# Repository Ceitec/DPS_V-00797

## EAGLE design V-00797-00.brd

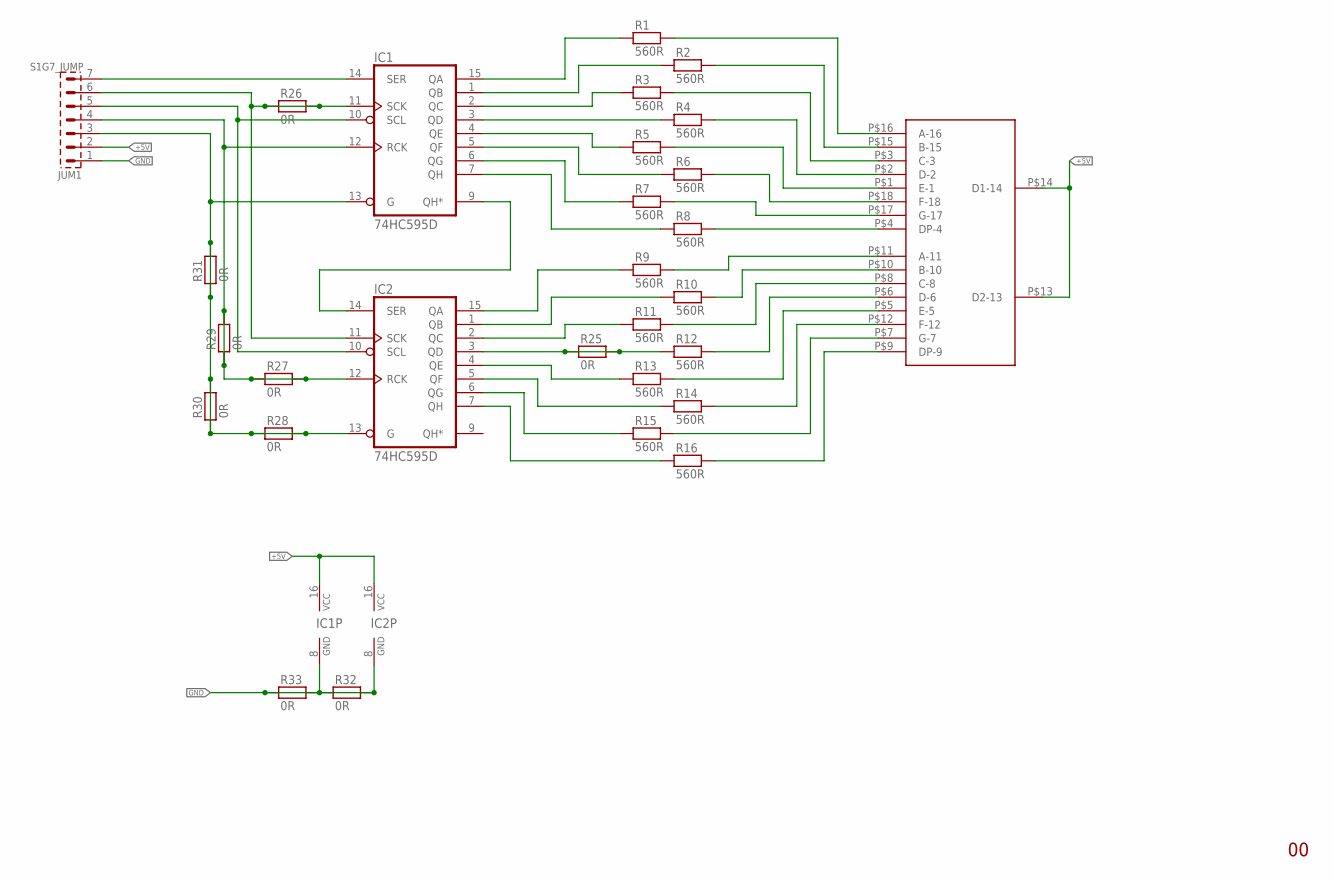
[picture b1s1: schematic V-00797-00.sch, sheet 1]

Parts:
IC1, IC2: 74HC595D; SO16
JUM1: S1G7_JUMP; S1G7_JUM
R1, R2, R3, R4, R5, R6, R7, R8, R9, R10, R11, R12, R13, R14, R15, R16: 560R; 1206
R25, R26, R27, R28, R29, R30, R31, R32, R33: 0R; 1206
U$1: BD-A544RD

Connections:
+5V: IC1.16 (VCC), IC2.16 (VCC), JUM1.2, U$1.P$13 (D2-13), U$1.P$14 (D1-14); also elsewhere on the board
GND: IC1.8 (GND), IC2.8 (GND), JUM1.1, R32.1, R32.2, R33.1, R33.2; also elsewhere on the board
unnamed: R1.2, U$1.P$16 (A-16)
unnamed: R2.2, U$1.P$15 (B-15)
unnamed: R3.2, U$1.P$3 (C-3)
unnamed: R4.2, U$1.P$2 (D-2)
unnamed: R5.2, U$1.P$1 (E-1)
unnamed: R6.2, U$1.P$18 (F-18)
unnamed: R7.2, U$1.P$17 (G-17)
unnamed: R8.2, U$1.P$4 (DP-4)
unnamed: IC1.9 (QH*), IC2.14 (SER)
unnamed: IC1.15 (QA), R1.1
unnamed: IC1.1 (QB), R2.1
unnamed: IC1.2 (QC), R3.1
unnamed: IC1.3 (QD), R4.1
unnamed: IC1.4 (QE), R5.1
unnamed: IC1.5 (QF), R6.1
unnamed: IC1.6 (QG), R7.1
unnamed: IC1.7 (QH), R8.1
unnamed: IC2.1 (QB), R10.1
unnamed: IC2.2 (QC), R11.1
unnamed: IC2.3 (QD), R12.1, R25.1, R25.2
unnamed: IC2.15 (QA), R9.1
unnamed: IC2.7 (QH), R16.1
unnamed: IC2.6 (QG), R15.1
unnamed: IC2.5 (QF), R14.1
unnamed: IC2.4 (QE), R13.1
unnamed: R9.2, U$1.P$11 (A-11)
unnamed: R10.2, U$1.P$10 (B-10)
unnamed: R11.2, U$1.P$8 (C-8)
unnamed: R12.2, U$1.P$6 (D-6)
unnamed: R13.2, U$1.P$5 (E-5)
unnamed: R14.2, U$1.P$12 (F-12)
unnamed: R15.2, U$1.P$7 (G-7)
unnamed: R16.2, U$1.P$9 (DP-9)
unnamed: IC1.14 (SER), JUM1.7
unnamed: IC1.11 (SCK), IC2.11 (SCK), JUM1.6, R26.1, R26.2
unnamed: IC1.10 (SCL), IC2.10 (SCL), JUM1.5
unnamed: IC1.12 (RCK), IC2.12 (RCK), JUM1.4, R27.1, R27.2, R29.1, R29.2
unnamed: IC1.13 (G), IC2.13 (G), JUM1.3, R28.1, R28.2, R30.1, R30.2, R31.1, R31.2

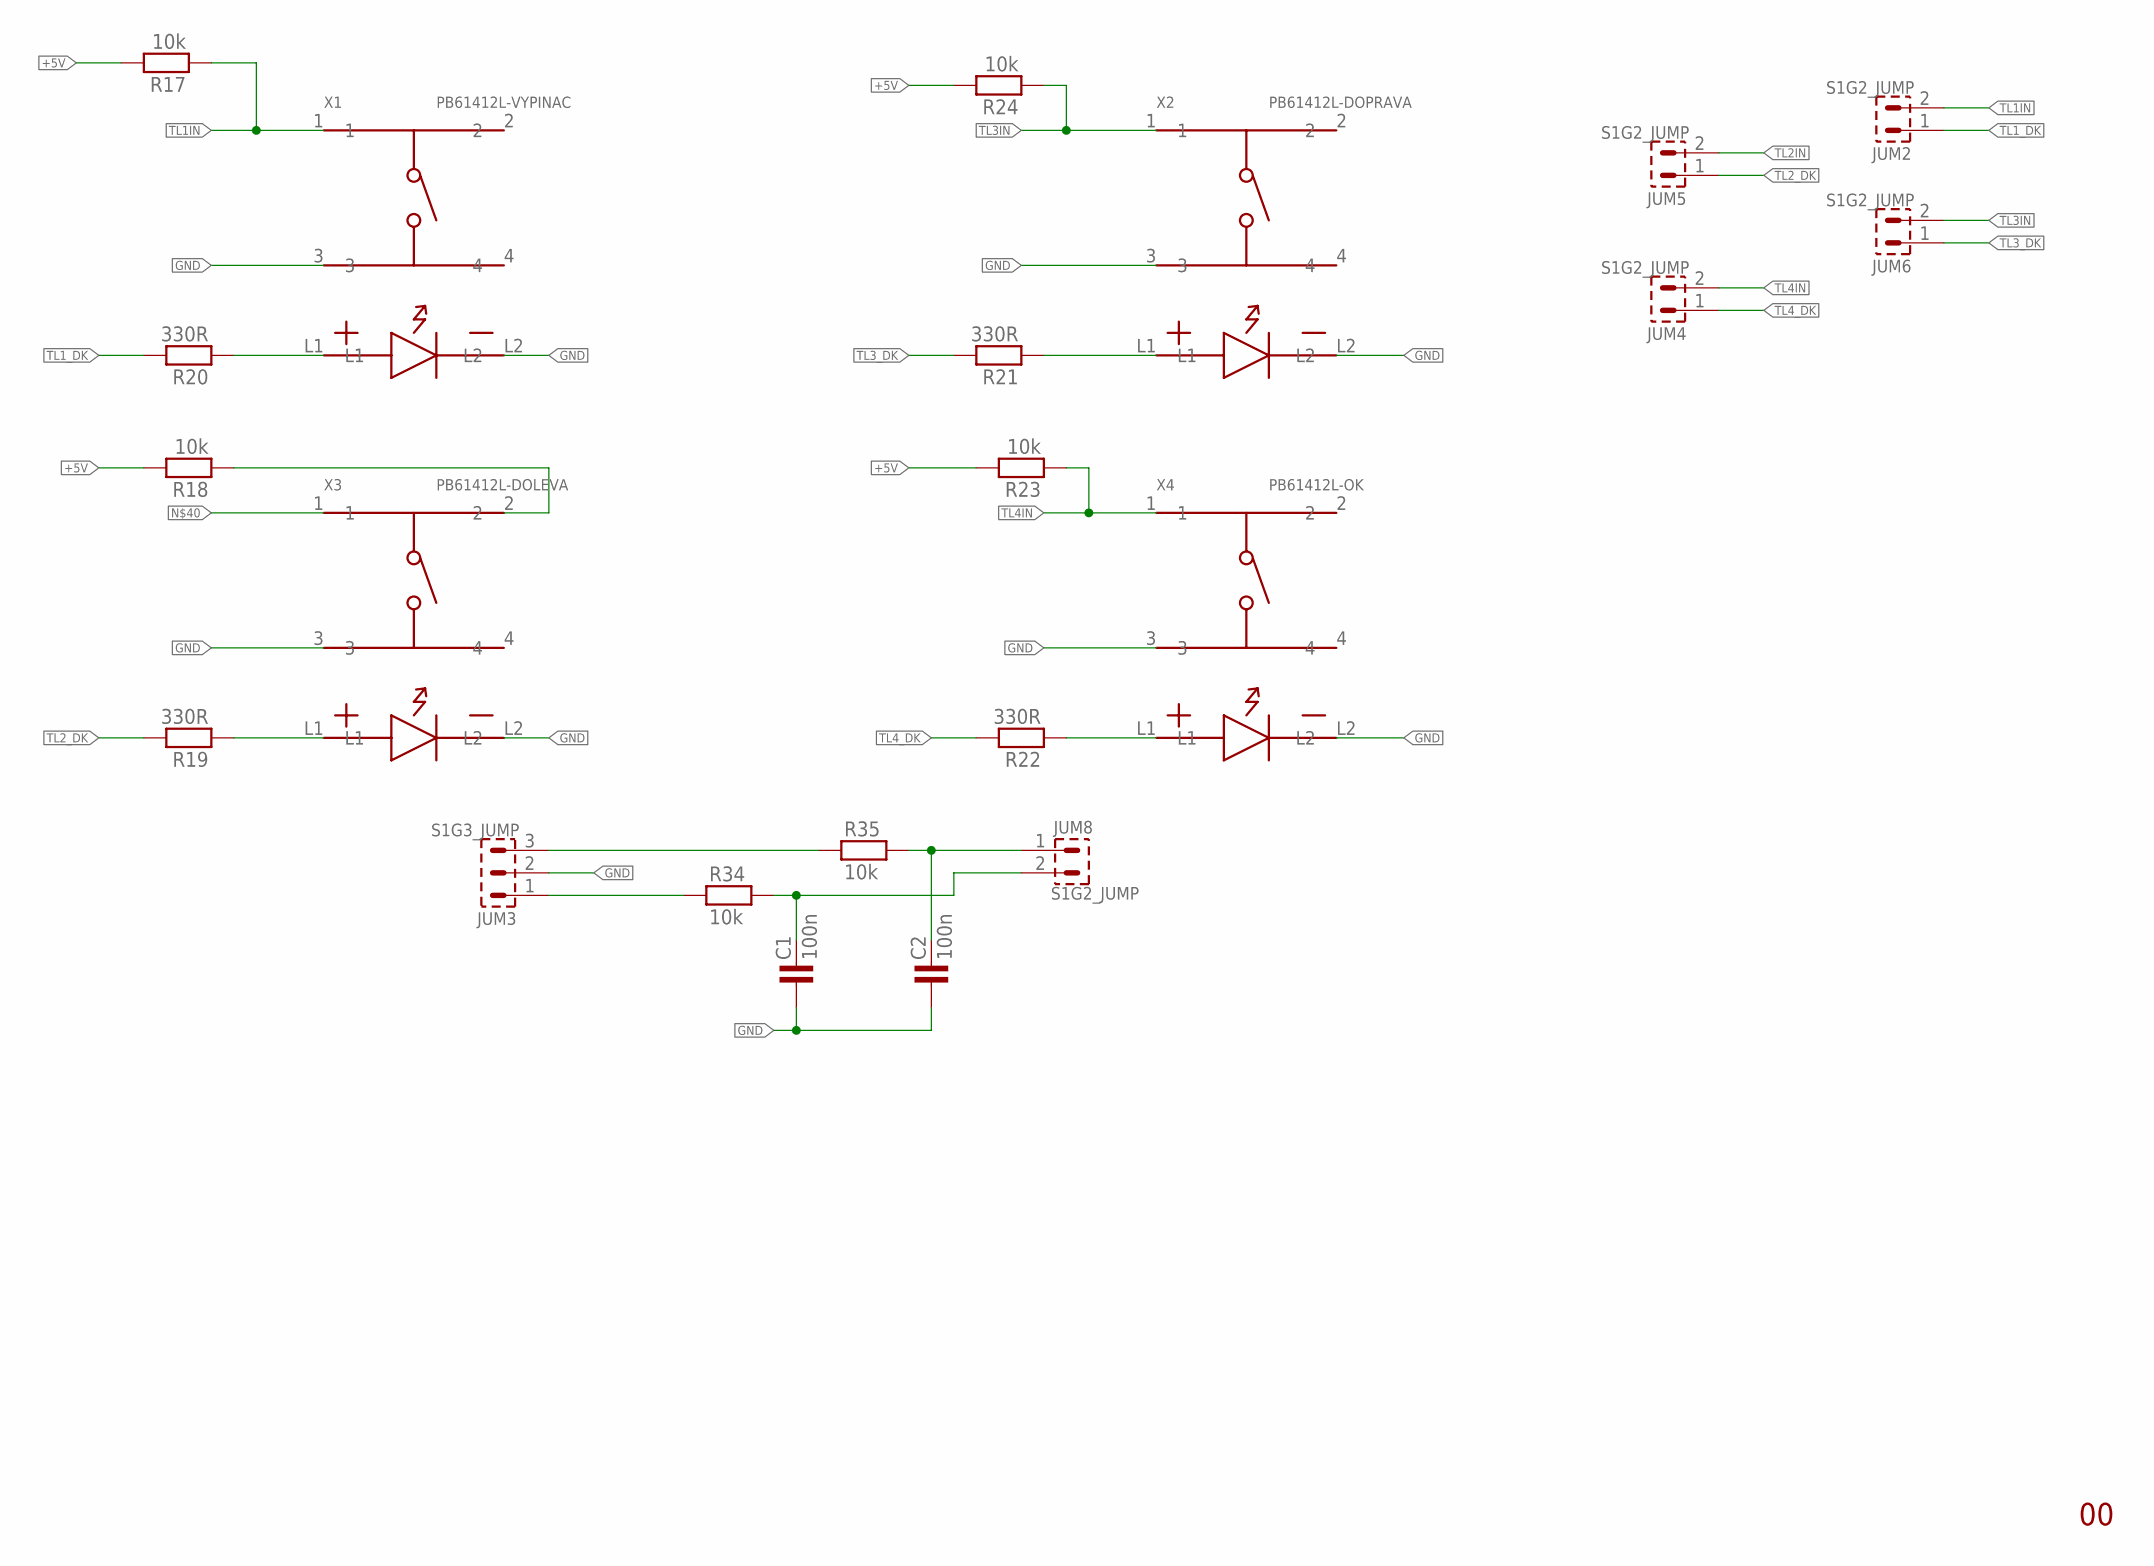
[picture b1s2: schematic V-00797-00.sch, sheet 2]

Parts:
C1, C2: 100n; 1206
JUM2, JUM4, JUM5, JUM6, JUM8: S1G2_JUMP; S1G2_JUM
JUM3: S1G3_JUMP; S1G3_JUM
R17, R18, R23, R24, R34, R35: 10k; 1206
R19, R20, R21, R22: 330R; 1206
X1: PB61412L-VYPINAC; PB1412L-101
X2: PB61412L-DOPRAVA; PB1412L-101
X3: PB61412L-DOLEVA; PB1412L-101
X4: PB61412L-OK; PB1412L-101

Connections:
+5V: R17.2, R18.2, R23.2, R24.2; also elsewhere on the board
ENCODER_A: JUM3.3, R35.1
ENCODER_B: JUM3.1, R34.1
GND: C1.1, C2.1, JUM3.2, X1.3, X1.L2, X2.3, X2.L2, X3.3, X3.L2, X4.3, X4.L2; also elsewhere on the board
INT1: C2.2, JUM8.1, R35.2
unnamed: R20.1, X1.L1
unnamed: R21.1, X2.L1
unnamed: R19.1, X3.L1
unnamed: R22.1, X4.L1
OCB1: C1.2, JUM8.2, R34.2
TL1IN: JUM2.2, R17.1, X1.1
TL1_DK: JUM2.1, R20.2
TL2IN: JUM5.2, R18.1, X3.2
TL2_DK: JUM5.1, R19.2
TL3IN: JUM6.2, R24.1, X2.1
TL3_DK: JUM6.1, R21.2
TL4IN: JUM4.2, R23.1, X4.1
TL4_DK: JUM4.1, R22.2

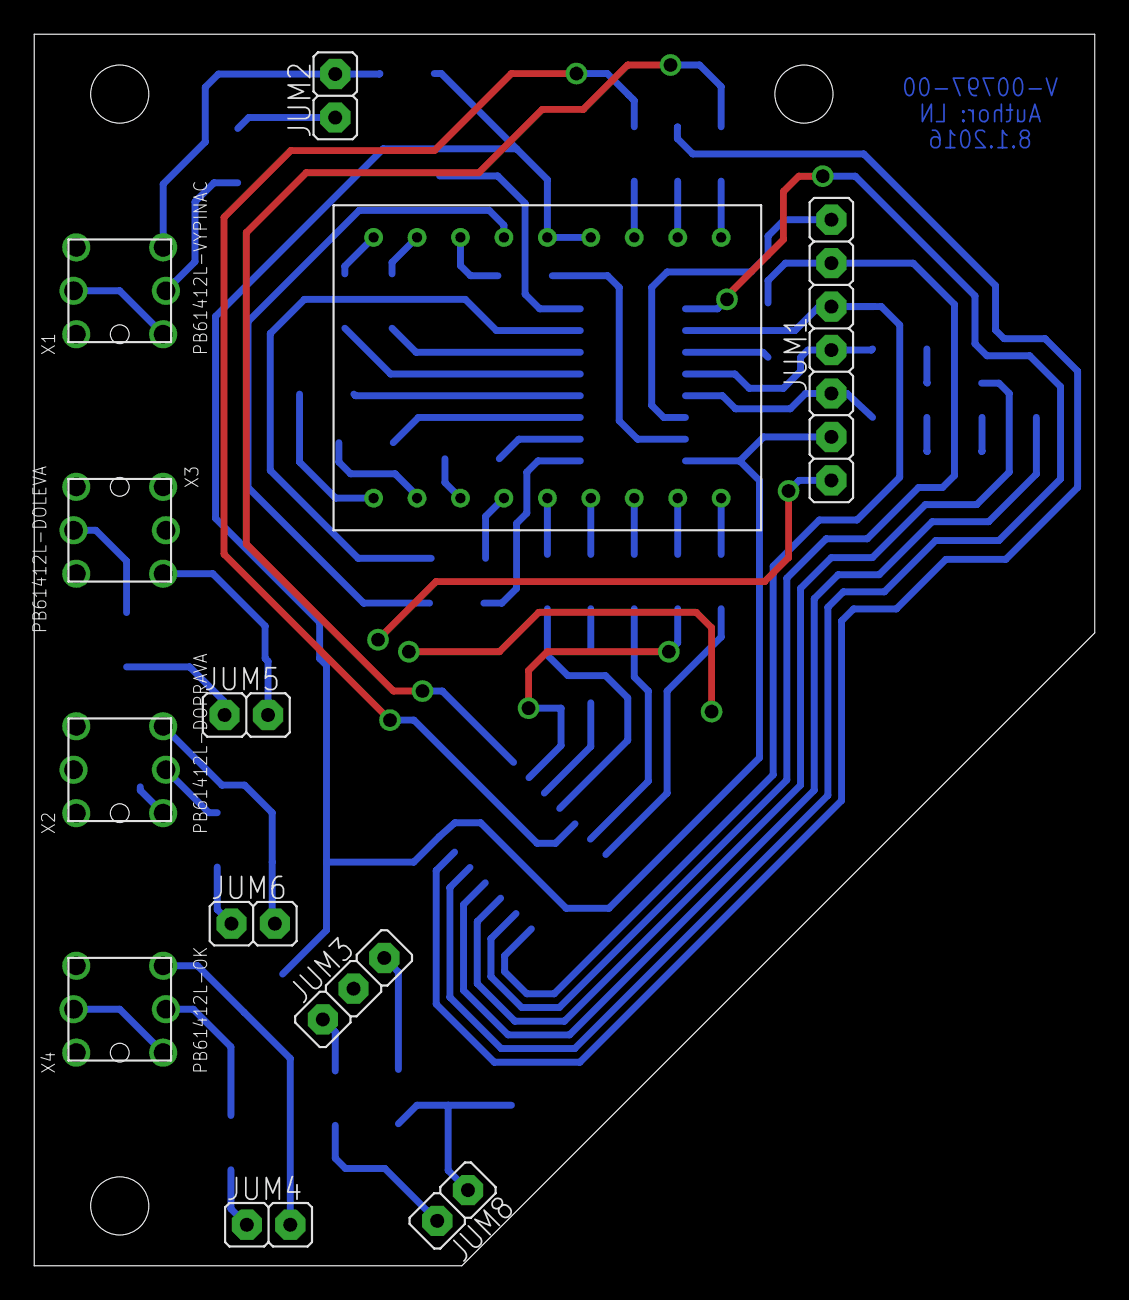
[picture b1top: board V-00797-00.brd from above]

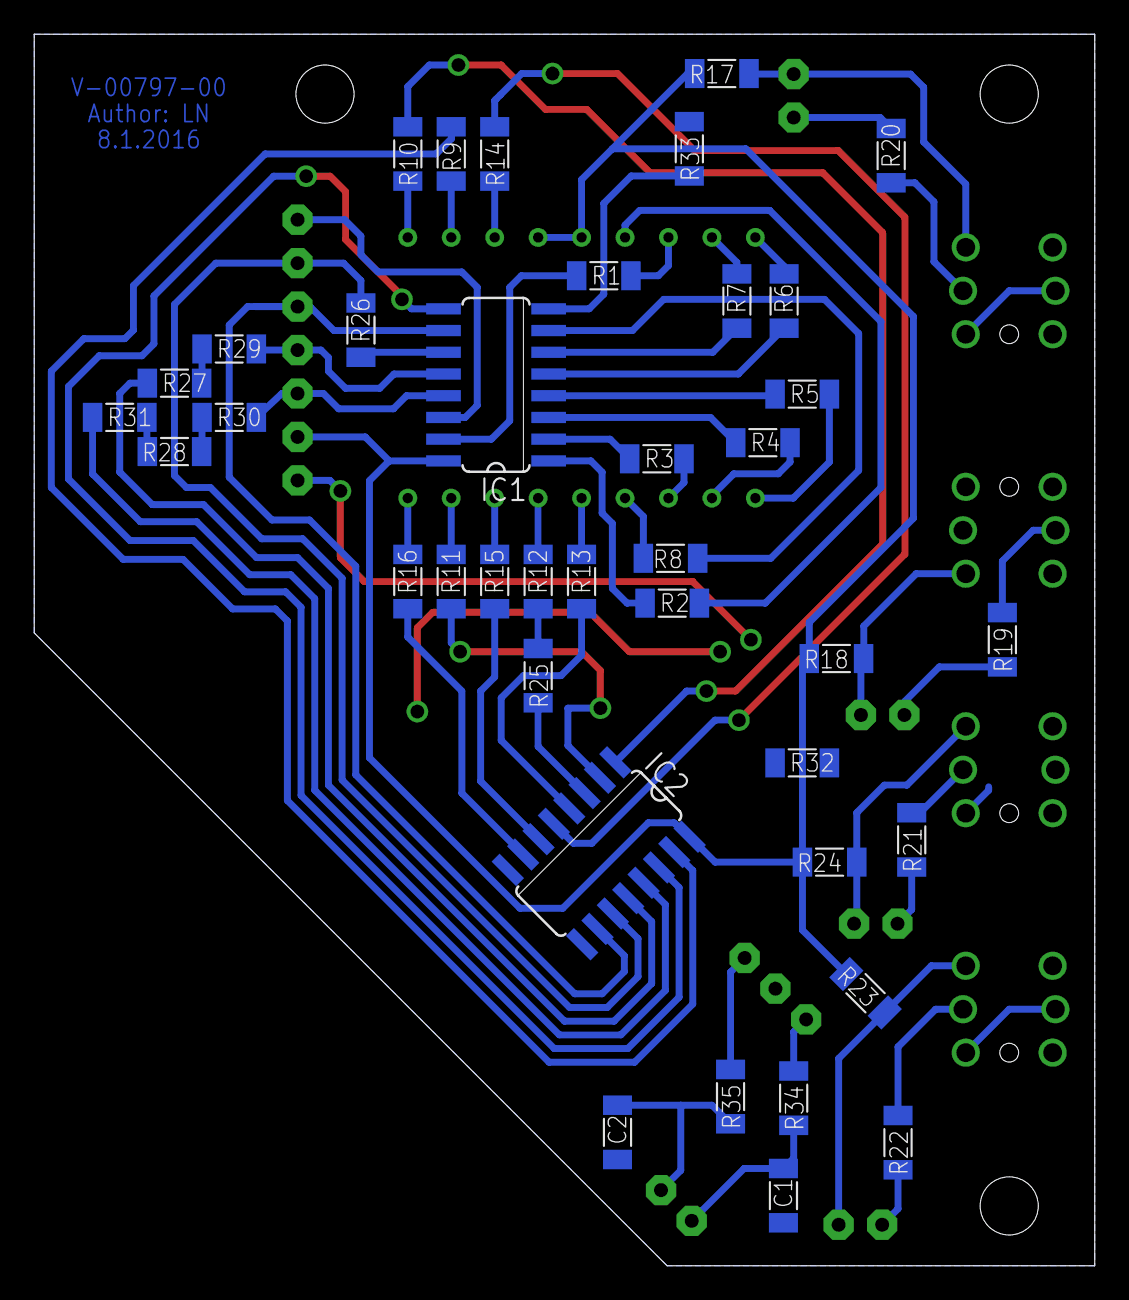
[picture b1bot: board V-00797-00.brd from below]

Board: 2 copper layers, 62.0 x 72.0 mm, 51 parts (39 on the bottom side), 56 nets.

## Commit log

2016-01-21 :circus_tent: Added .gitattributes & .gitignore files
2016-01-21 v.1.0.0
    Prvotni verze pro BM6
2016-01-21 v.1.0.1
    Verze ne BM6 ale je to Joystick
2016-02-10 v.2.0

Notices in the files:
parts and their libraries:
Copyright (C) PaJa 2011-2014
Copyright (C) PaJa 2001-2014
